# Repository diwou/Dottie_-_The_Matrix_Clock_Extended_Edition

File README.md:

# Dottie - The Matrix Clock 'Extended Version'

Eine Dot-Matrix-Uhr auf Basis einer **ESP32-S3-WROOM-1-N16R8-Platine** mit 16 MAX7219-LED-Matrix-Modulen, DS3231-RTC mit CR2032-Pufferung und VEML7700-Lichtsensor. Die Uhr zeigt Zeit und Datum mit Scroll-Animation, regelt die Helligkeit automatisch nach Umgebungslicht, synchronisiert die hochgenaue RTC per NTP und bietet eine Weboberfläche für Konfiguration, Diagnose, manuelle RTC-Einstellung und Firmware-Upload.

<p>
  
</p>

- Aktuelle Version: `1.6.0` (Development-Builds zeigen zusätzlich den Codeberg-Kurz-Hash)
- Repository: `https://codeberg.org/diwou/Dottie_-_The_Matrix_Clock_Extended_Edition`
- Browser-Installer: [https://diwou.codeberg.page/Dottie_-_The_Matrix_Clock/](https://diwou.codeberg.page/Dottie_-_The_Matrix_Clock/)
- Web-UI im Gerät: [http://dottie.local/](http://dottie.local/) im lokalen Netz
- Lizenz: `CC BY-NC-SA 4.0`

---

## Features

- **Zeitbasis**: DS3231-RTC als Laufzeit-Uhr, NTP zur regelmäßigen Korrektur und manuelle RTC-Einstellung im Webinterface
- **NTP-Synchronisation** mit 3 konfigurierbaren Fallback-Servern
- **Zeitzone & DST**: UTC-Offset, EU/US/Custom-Sommerzeit
- **Display**: 24h/12h-Modus, 5 Datumsformate, einstellbare Helligkeit, Scroll-Animation, Software-Dimmen und VEML7700-Autohelligkeit
- **Web-UI**: Responsive HTML5-Oberfläche mit Live-Display-Vorschau, RTC-Tab, NTP-Status, Diagnose, Firmware-Installer und umschaltbarem Light-/Dark-Mode
- **OTA-/Firmware-Updates**: Kabellose Updates über `dottie.local` und Web-Upload von `.bin`-Firmwaredateien
- **WiFi-Resilienz**: State-Machine mit exponentiellem Backoff, AP-Fallback (Captive Portal)
- **Factory-Reset**: konfigurierbarer GPIO 5 Sekunden halten

---

## Hardware

| Komponente | Details |
|---|---|
| MCU | ESP32-S3-WROOM-1-N16R8 |
| Display | 16× MAX7219 LED-Matrix-Module (FC16_HW) |
| Display-Pins | DIN = GPIO11, CLK = GPIO12, CS/LOAD = GPIO10 |
| I2C | SDA = GPIO38, SCL = GPIO39 für VEML7700 und DS3231S |
| RTC | DS3231S als Laufzeit-Uhr, CR2032-batteriegepuffert, NTP schreibt Korrekturen zurück in die RTC |
| Anordnung | 2 Reihen: TOP (8 Module, 8×8 px) + BOTTOM (8 Module, 5×7 px) |
| Reset-Button | GPIO9 gegen GND, 5 Sekunden halten |

## KiCad

Der KiCad-Projektspiegel liegt unter [kicad/README.md](kicad/README.md).

| Pfad | Inhalt |
|---|---|
| `kicad/source/` | KiCad-Quellen des Boards |
| `kicad/fab/rev0.4/` | Fertigungsdaten für die aktuelle Hardwarefreigabe `0.4` |

Die vollständige Stückliste liegt in `kicad/fab/rev0.4/bom.csv`, die zugehörigen Bestückungsdaten in `positions.csv` und die Freigabe als Paket in `Dottie_-_The_Matrix_Clock_0.4.zip`.

### Verdrahtung

```
ESP32-S3 → MAX7219-Kette
GPIO11 → DIN
GPIO12 → CLK
GPIO10 → CS/LOAD
```

Die Pinwerte werden in `platformio.ini` über `DISPLAY_DATA_PIN`, `DISPLAY_CLK_PIN`, `DISPLAY_CS_PIN`, `FACTORY_RESET_PIN`, `I2C_SDA_PIN` und `I2C_SCL_PIN` gesetzt.

Die 16 Module bilden eine SPI-Kette: TOP (Module 0–7, rechts nach links) und BOTTOM (Module 8–15, rechts nach links). Das physikalische Mapping wird über `MAP_TOP[]` und `MAP_BOTTOM[]` in `display.h` konfiguriert.

---

## Software / Build

**Werkzeug:** PlatformIO (VSCode/VSCodium Extension oder CLI)

```bash
# Kompilieren
pio run -e dottie_esp32s3

# OTA-Upload (IP per CLI angeben)
pio run -t upload -e dottie_esp32s3_ota --upload-port dottie.local

# Wenn das Board nur im AP-Modus laeuft:
# pio run -t upload -e dottie_esp32s3_ota --upload-port 192.168.4.1

# VS Codium: Task "PIO OTA Upload (ESP32-S3)"
# (nutzt das OTA-Env direkt und umgeht den fehlerhaften Upload-Dialog)

# Native USB am ESP32-S3
pio run -t upload -e dottie_esp32s3 --upload-port /dev/serial/by-id/usb-Espressif_USB_JTAG_serial_debug_unit_94-A9-90-2F-91-A0-if00

# Firmware-Build-Artefakte
# `Firmware/<version>/` und `Firmware/latest/` werden beim Build automatisch erzeugt

# Firmware-Installer im Webinterface
# Im Web-UI unter `System` -> `Firmware-Installer` die `.bin` aus `Firmware/latest/` hochladen.

# Serieller Monitor (USB-Fallback, 115200 Baud)
pio device monitor
```

### Abhängigkeiten

| Bibliothek | Version |
|---|---|
| `majicdesigns/MD_MAX72XX` | ^3.5.1 |
| `adafruit/Adafruit VEML7700 Library` | ^2.1.6 |
| ESP32 Arduino Core (PlatformIO `espressif32`) | – |

---

## Inbetriebnahme

1. Firmware per USB oder OTA flashen; bei OTA die Geräte-IP über `--upload-port` angeben
2. Firmware flashen: `pio run -t upload -e dottie_esp32s3`
3. Beim ersten Start ohne gespeicherte WLAN-Konfiguration öffnet Dottie einen **AP** mit SSID `DOTTIE-{ChipID}`
4. Mit dem AP verbinden (IP: `192.168.4.1`) und WLAN-Zugangsdaten eingeben
5. Nach dem Verbinden ist die Web-UI unter der zugewiesenen IP oder `http://dottie.local` erreichbar

---

## Web-Oberfläche

### Tabs

| Tab | Inhalt |
|---|---|
| **Status** | WiFi-Status, IP, NTP-Log (letzte 5 Syncs), manueller NTP-Test |
| **WiFi** | SSID, Passwort, Timeout, DHCP/Static-IP, DNS |
| **NTP** | 3 Server-URLs, Sync-Intervall, Test-Buttons |
| **RTC** | DS3231-Status, I2C-Diagnose, letzter NTP-Sync, manuelle Uhrzeit/Datum-Eingabe |
| **Zeitzone** | UTC-Offset, DST-Modus (Aus/EU/US/Custom) |
| **Display** | 24h/12h, Sekunden, Datumsformat, Helligkeit, Scroll-Effekt, VEML7700-Autohelligkeit |
| **System** | OTA, Firmware-Installer, Dark-Mode, Chip-Info, Neustart, Factory-Reset, Diagnose |

### REST-API

| Endpoint | Methode | Beschreibung |
|---|---|---|
| `/api/status` | GET | JSON: Zeit, Datum, Uptime, next_sync, Heap, RSSI |
| `/api/ntptest` | GET | JSON: running, host, result, detail |
| `/api/update` | POST | Firmware per Web-Upload einspielen |
| `/rtcset` | POST | RTC manuell auf Datum und Uhrzeit setzen |
| `/save` | POST | Konfiguration speichern |
| `/test?i=1..3` | POST | NTP-Server testen (asynchron) |
| `/reboot` | POST | Neustart |
| `/factory` | POST | Factory-Reset |
| `/diag` | GET | Diagnose-Seite (Debug-Info) |

---

## Konfiguration

Die Konfiguration wird als `Key=Value`-Datei auf LittleFS unter `/cfg.txt` gespeichert. Kommentare mit `#` sind erlaubt.

### Wichtige Parameter

| Schlüssel | Standardwert | Beschreibung |
|---|---|---|
| `ntp1..3` | pool.ntp.org, time.google.com, time.cloudflare.com | NTP-Server |
| `ntp_interval_min` | 15 | Sync-Intervall in Minuten (0 = 15) |
| `utc_offset_min` | 60 | UTC-Offset in Minuten (UTC+1 = 60) |
| `dst_mode` | 1 | 0=Aus, 1=EU, 2=US, 3=Custom |
| `date_fmt` | 0 | Datumsformat (0–4, s.u.) |
| `show_24h` | 1 | 24h-Modus (0 = 12h mit AM/PM) |
| `show_seconds` | 1 | Sekunden anzeigen (nur 24h) |
| `brightness` | 1 | Display-Helligkeit (0–15) |
| `auto_brightness` | 0 | Helligkeit automatisch per VEML7700 regeln |
| `scroll_enabled` | 1 | Scroll-Animation beim Ziffernwechsel |
| `pwm_duty` | 10 | Software-Dimmen (10 = aus, 1–5 = 10–50 % Abdunklung) |

### Datumsformate

| Wert | Format | Beispiel |
|---|---|---|
| 0 | `DD.MM.YYYY` | 07.03.2026 |
| 1 | `MM/DD/YYYY` | 03/07/2026 |
| 2 | `YYYY-MM-DD` | 2026-03-07 |
| 3 | `DD.MM.YY` | 07.03.26 |
| 4 | `MM/DD/YY` | 03/07/26 |

---

## Architektur

### Dateistruktur

| Datei | Rolle |
|---|---|
| `src/main.cpp` | Kernlogik: Boot, WiFi-State-Machine, NTP-Sync, OTA, Loop |
| `src/config.h` | Config-Struct, LittleFS-Load/Save (`/cfg.txt`), Makro-Parser, `APP_VERSION_BASE` |
| `src/display.h` | Bitmap-Glyphen (8×8 + 5×7), Scroll-Animation, Display-Mapping |
| `src/webserver.h` | HTML5-WebUI (Tabs), REST-APIs, JavaScript-Glyphen-Renderer |
| `platformio.ini` | Build-Konfiguration, Bibliotheksabhängigkeiten |

### WiFi-State-Machine

```
CONNECTED
  ↓ (Verbindungsverlust)
DISCONNECTED
  ↓ (nach Backoff: 30s → 60s → 120s → 300s max)
RECONNECTING
  ↓ (max. Fehlversuche erreicht)
AP_MODE (Captive Portal: SSID DOTTIE-{ChipID}, IP 192.168.4.1)
```

### NTP-Synchronisation

1. DNS-Auflösung (3 Versuche, lwIP-Direktfallback)
2. IP-Cache (3 Einträge) für schnelle Re-Syncs
3. UDP-Probe nach RFC 5905, Timeout 900 ms
4. 3 Server werden getestet, erster erfolgreicher wird verwendet
5. Log-Ringpuffer (5 Einträge) in der Web-UI sichtbar

### Display-Mapping

Physikalische Modul-IDs werden über `MAP_TOP[8]` und `MAP_BOTTOM[8]` von logischen Positionen entkoppelt. Flip/Mirror/Rotate für das Bottom-Display sind über Defines konfigurierbar (`BOTTOM_FLIP_VERTICAL_8`).

### OTA

- Hostname: `dottie.local` (mDNS)
- Progress-Anzeige auf dem Matrix-Display (Prozentbalken)
- OTA-Passwort optional konfigurierbar

---

## Factory-Reset

Den in `FACTORY_RESET_PIN` konfigurierten GPIO für **5 Sekunden** gegen GND halten:
- Countdown wird auf dem Display angezeigt
- `/cfg.txt` wird gelöscht
- Gerät startet neu und öffnet AP

---

## Lizenz

Dieses Projekt steht unter der Lizenz `Creative Commons Attribution-NonCommercial-ShareAlike 4.0 International (CC BY-NC-SA 4.0)`.

Lizenztext: `LICENSE`

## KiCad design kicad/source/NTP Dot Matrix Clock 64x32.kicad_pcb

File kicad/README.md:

# KiCad-Projektspiegel

Hier liegt der importierte KiCad-Stand von Dottie. Die Struktur folgt dem Muster aus den anderen Board-Projekten: `source/` enthält die KiCad-Quellen, `fab/rev0.4/` die Freigabe- und Fertigungsdaten.

## Struktur

| Pfad | Inhalt |
|---|---|
| `source/` | KiCad-Projektdateien, Schaltplan, Platine, Blockbibliothek und projektbezogene Hilfsdateien |
| `fab/rev0.5/` | Fertigungsdaten für die freigegebene Version `0.5` |

## Fertigungsdaten

Die aktuelle Freigabe liegt in `fab/rev0.5/`:

- `bom.csv` - Stückliste
- `designators.csv` - Zuordnung der Bauteilbezeichner
- `netlist.ipc` - IPC-1791-Netzliste
- `positions.csv` - Bestückungskoordinaten
- `Dottie_-_The_Matrix_Clock_0.5.zip` - kompletter Export der Fertigungslage

## Stückliste in Kurzform

Die vollständige Stückliste steht in `fab/rev0.5/bom.csv`. Die wichtigsten Funktionsbausteine sind:

| Bauteil | Menge | Rolle |
|---|---:|---|
| `MAX7219CWG` | 16 | LED-Matrix-Treiber für die 16 Module |
| `ESP32-S3-WROOM-1` | 1 | Haupt-MCU |
| `DS3231S` | 1 | hochgenaue RTC mit `CR2032`-Pufferung |
| `VEML7700-TT` | 1 | Umgebungslichtsensor |
| `TLV76133DCY` | 1 | 3.3-V-Versorgung |
| `74HCT245` | 1 | Pegel-/Bus-Treiber |
| `USB-C-Receptacle` | 1 | USB-Anschluss der Platine |
| `BatteryHolder_CR2032` | 1 | Pufferbatterie für die RTC |

## Hinweise

- Die KiCad-Quellen gehören nach `source/`.
- Fertigungsdaten gehören nach `fab/rev0.5/`.
- Änderungen an der Platine werden im Changelog des Firmware-Repos mit aufgeführt, damit Firmware- und Hardware-Stand zusammenbleiben.

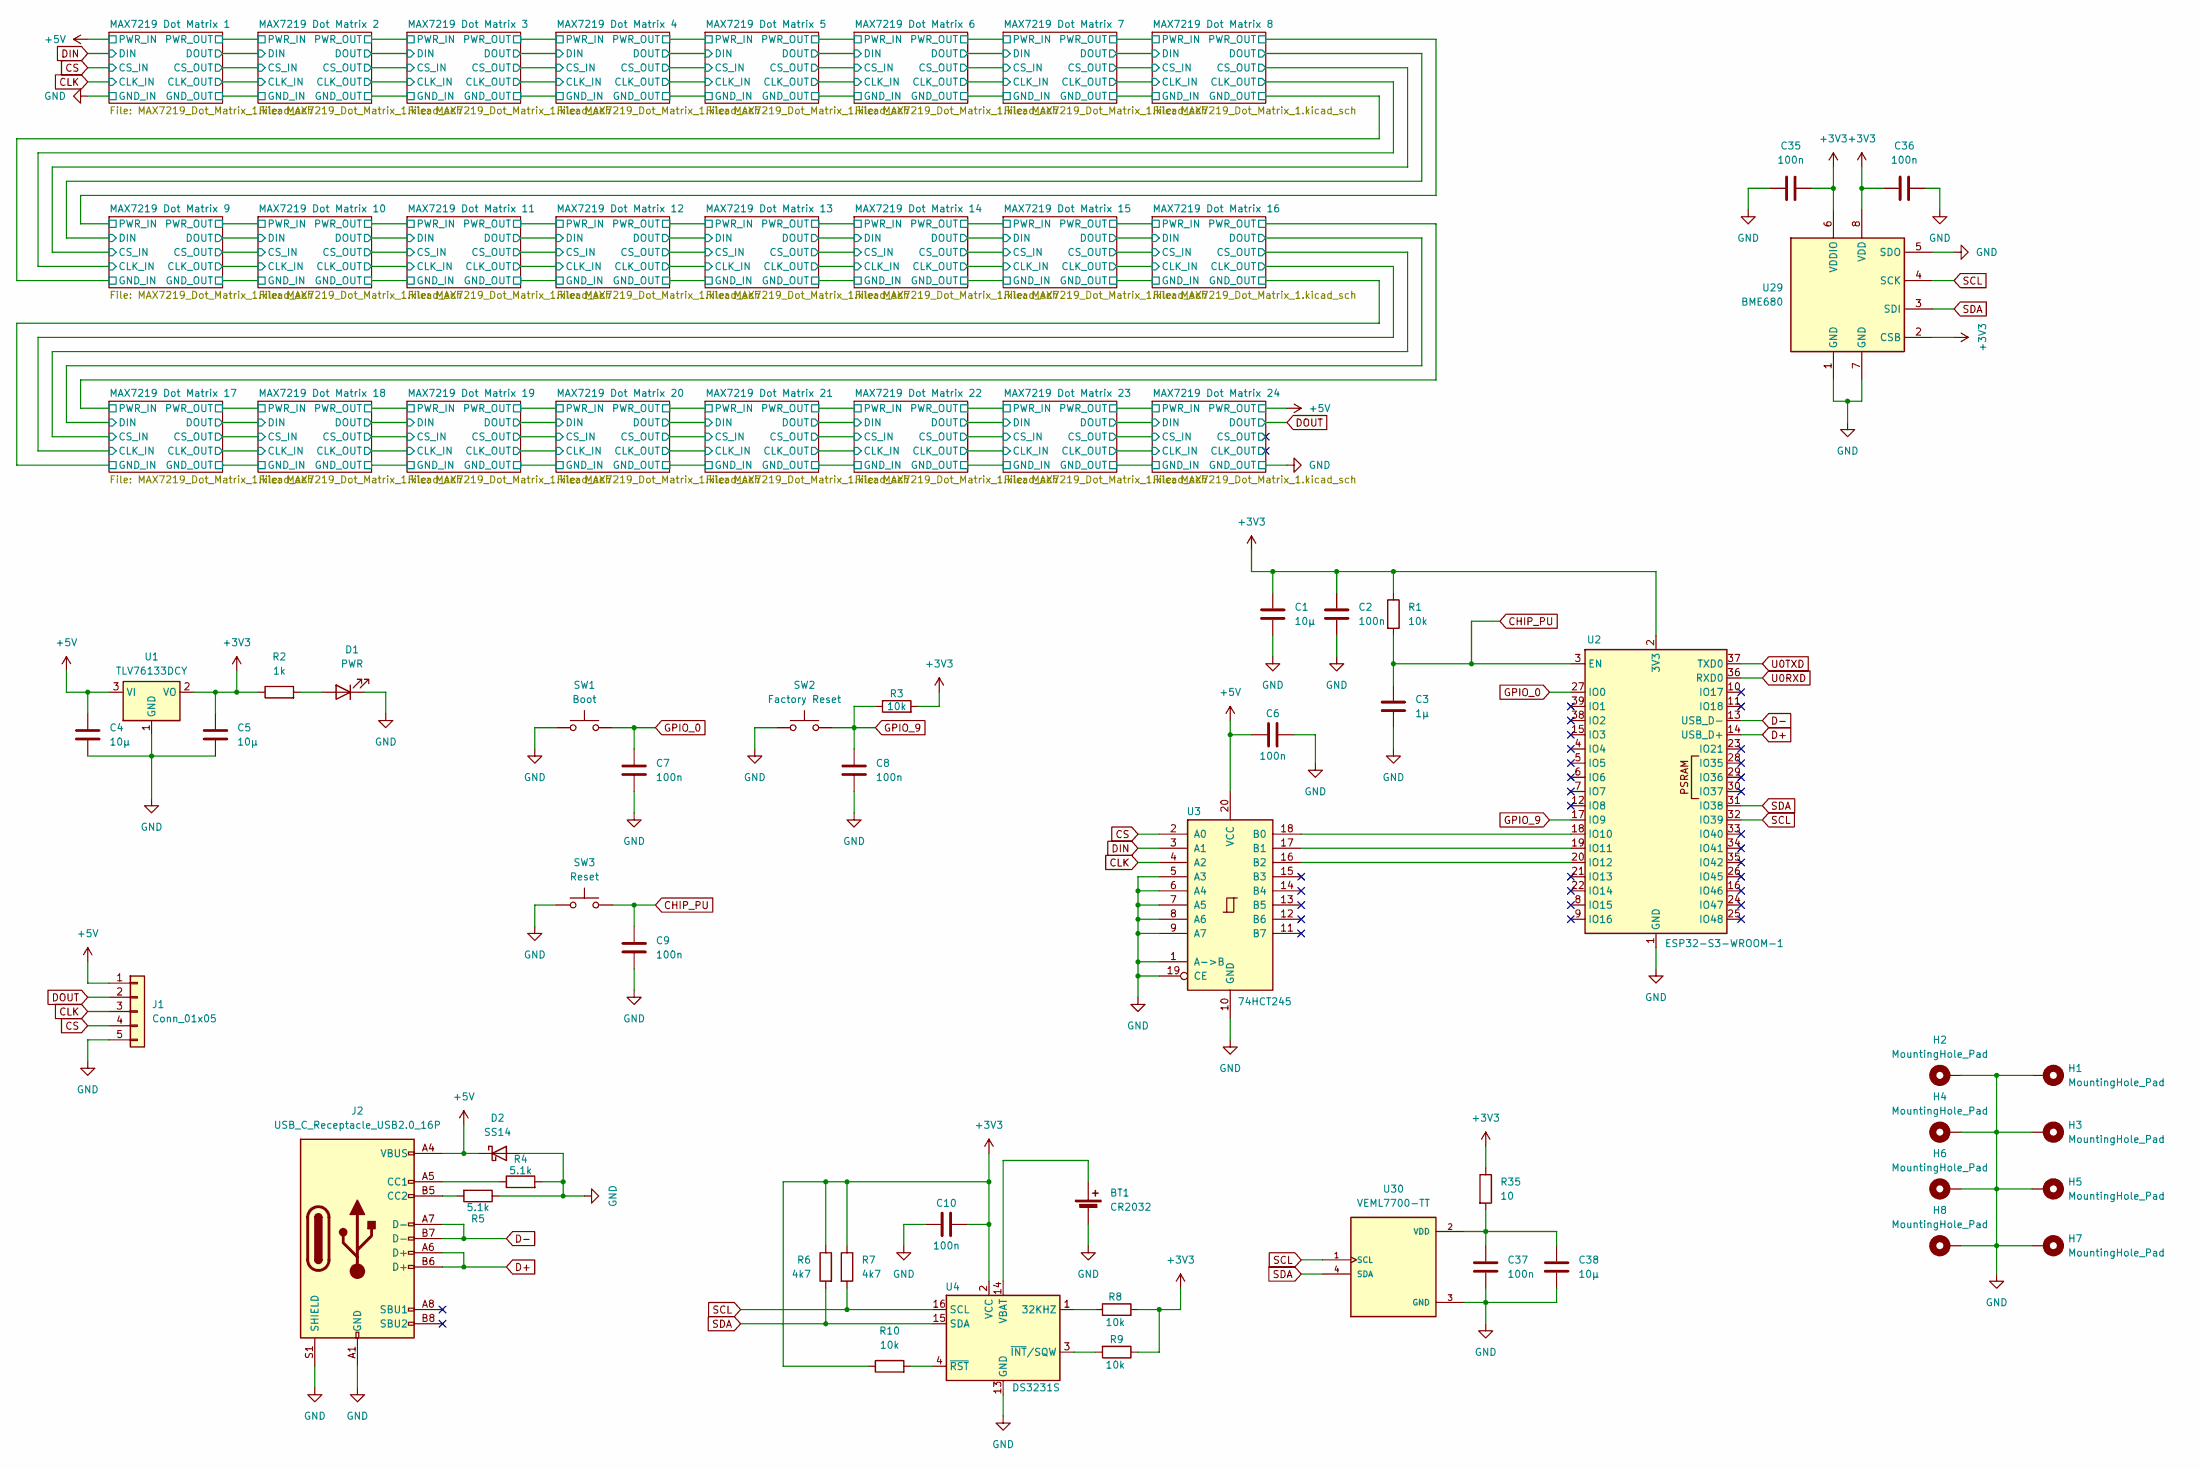
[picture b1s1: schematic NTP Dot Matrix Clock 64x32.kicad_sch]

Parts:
BT1: CR2032; BatteryHolder_MYOUNG_BS-07-A1BJ001_CR2032
C1, C38: 10µ; C_0805_2012Metric_Pad1.18x1.45mm_HandSolder
C2, C6, C7, C8, C9, C10, C35, C36, C37: 100n; C_0805_2012Metric_Pad1.18x1.45mm_HandSolder
C3: 1µ; C_0805_2012Metric_Pad1.18x1.45mm_HandSolder
C4, C5: 10µ; C_1206_3216Metric_Pad1.33x1.80mm_HandSolder
D1: PWR; LED_0805_2012Metric_Pad1.15x1.40mm_HandSolder
D2: SS14; D_SMA
H1, H2, H3, H4, H5, H6, H7, H8: MountingHole_Pad; MountingHole_3.2mm_M3_DIN965_Pad
J1: Conn_01x05; PinHeader_1x05_P2.54mm_Vertical
J2: USB_C_Receptacle_USB2.0_16P; USB_C_Receptacle_HCTL_HC-TYPE-C-16P-01A
R1, R3, R8, R9, R10: 10k; R_0805_2012Metric_Pad1.20x1.40mm_HandSolder
R2: 1k; R_0805_2012Metric_Pad1.20x1.40mm_HandSolder
R4, R5: 5.1k; R_0805_2012Metric_Pad1.20x1.40mm_HandSolder
R6, R7: 4k7; R_0805_2012Metric_Pad1.20x1.40mm_HandSolder
R35: 10; R_0805_2012Metric_Pad1.20x1.40mm_HandSolder
SW1: Boot; SW_PUSH_6mm_H5mm
SW2: Factory Reset; SW_PUSH_6mm_H5mm
SW3: Reset; SW_PUSH_6mm_H5mm
U1: TLV76133DCY; SOT-223-3_TabPin2
U2: ESP32-S3-WROOM-1
U3: 74HCT245; TSSOP-20_4.4x6.5mm_P0.65mm
U4: DS3231S; SOIC-16W_7.5x10.3mm_P1.27mm
U29: BME680; Bosch_LGA-8_3x3mm_P0.8mm_ClockwisePinNumbering
U30: VEML7700-TT; XDCR_VEML7700-TT; PARTREV 1.6

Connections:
+3V3: C1.1, C2.1, C5.1, C10.2, C35.2, C36.1, R1.1, R2.1, R3.2, R6.1, R7.1, R8.2, R9.1, R10.1, R35.1, U1.2 (VO), U2.2 (3V3), U4.2 (VCC), U29.2 (CSB), U29.6 (VDDIO), U29.8 (VDD)
+5V: C4.1, C6.1, D2.1 (K), J1.1, J2.A4 (VBUS), J2.A9 (VBUS), J2.B4 (VBUS), J2.B9 (VBUS), U1.3 (VI), U3.20 (VCC); also elsewhere on the board
CHIP_PU: C3.1, C9.1, R1.2, SW3.2, U2.3 (EN)
CLK: J1.3, U3.4 (A2); also elsewhere on the board
CS: J1.4, U3.2 (A0); also elsewhere on the board
D+: J2.A6 (D+), J2.B6 (D+), U2.14 (USB_D+)
D-: J2.A7 (D-), J2.B7 (D-), U2.13 (USB_D-)
DIN: U3.3 (A1); also elsewhere on the board
DOUT: J1.2; also elsewhere on the board
GND: BT1.2 (-), C1.2, C2.2, C3.2, C4.2, C5.2, C6.2, C7.2, C8.2, C9.2, C10.1, C35.1, C36.2, C37.2, C38.2, D1.1 (K), D2.2 (A), H1.1 (1_1), H2.1 (1_1), H3.1 (1_1), H4.1 (1_1), H5.1 (1_1), H6.1 (1_1), H7.1 (1_1), H8.1 (1_1), J1.5, J2.A1 (GND), J2.A12 (GND), J2.B1 (GND), J2.B12 (GND), J2.S1 (SHIELD), R4.2, R5.1, SW1.1, SW2.1, SW3.1, U1.1 (GND), U2.1 (GND), U2.40 (GND), U2.41 (GND), U3.1 (A->B), U3.5 (A3), U3.6 (A4), U3.7 (A5), U3.8 (A6), U3.9 (A7), U3.10 (GND), U3.19 (CE), U4.5 (GND), U4.6 (GND), U4.7 (GND), U4.8 (GND), U4.9 (GND), U4.10 (GND), U4.11 (GND), U4.12 (GND), U4.13 (GND), U29.1 (GND), U29.5 (SDO), U29.7 (GND), U30.3 (GND); also elsewhere on the board
GPIO_0: C7.1, SW1.2, U2.27 (IO0)
GPIO_9: C8.1, R3.1, SW2.2, U2.17 (IO9)
unnamed: BT1.1 (+), U4.14 (VBAT)
unnamed: D1.2 (A), R2.2
unnamed: J2.A5 (CC1), R4.1
unnamed: J2.B5 (CC2), R5.2
unnamed: U2.18 (IO10), U3.18 (B0)
unnamed: U2.19 (IO11), U3.17 (B1)
unnamed: U2.20 (IO12), U3.16 (B2)
unnamed: R8.1, U4.1 (32KHZ)
unnamed: R9.2, U4.3 (~INT/SQW)
unnamed: R10.2, U4.4 (~RST)
unnamed: C37.1, C38.1, R35.2, U30.2 (VDD)
SCL: R7.2, U2.32 (IO39), U4.16 (SCL), U29.4 (SCK), U30.1 (SCL)
SDA: R6.2, U2.31 (IO38), U4.15 (SDA), U29.3 (SDI), U30.4 (SDA)
U0RXD: U2.36 (RXD0)
U0TXD: U2.37 (TXD0)

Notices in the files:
kicad/source/NTP Dot Matrix Clock 64x32.kicad_pcb:
© 2026  Dirk Wouters
License: CC BY-NC-SA 4.0
